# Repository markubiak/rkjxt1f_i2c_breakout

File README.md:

Alps RKJXT1F42001 7-Way Switch and Encoder I2C Breakout
-------------------------------------------------------

I2C breakout for Alps RKJXT1F42001 using Adafruit Seesaw library on the SAMD09.
Schematic is a copy of the I2C "Stemma QT" Rotary Encoder breakout board
(product 4991), though the NeoPixel and 2x STEMMA QT (JST SH 4-pin) connectors
had to be dropped due to layout constraints. The RKJXT1F is a significantly
larger through-hole device than the rotary encoder and the Stemma QT connectors
simply would not fit in their original locations. However, identical board
shape (1in x 1in) and mounting holes were retained. Due to an oversight, the
pin ordering in the through-hole connection was flipped from the reference
design.

Pins were kept the same as the reference design, so the firmware built on main
branch of adafruit/seesaw works laregly correctly. There is a difference in how
the RKJXT1F handles the rotary encoding compared to typical encoders, so a fork
of the seesaw library is pushed and pending merge back to main. With the
updated firmware, the I2C protocol works as intended. The GPIO Seesaw registers
can be used for the new A/B/C/D pins.

| Direction | GPIO Number |
|-----------|-------------|
| A         | 16          |
| B         | 17          |
| C         | 7           |
| D         | 2           |
| PUSH      | 24          |

The logic to handle the directions is simple enough to not require integration
into the seesaw library. Per the RKJXT1F datasheet, when PUSH goes active
(low), check if any of A/B/C/D are also active (low). If so, it's a directional
press. Else, it was a PUSH.

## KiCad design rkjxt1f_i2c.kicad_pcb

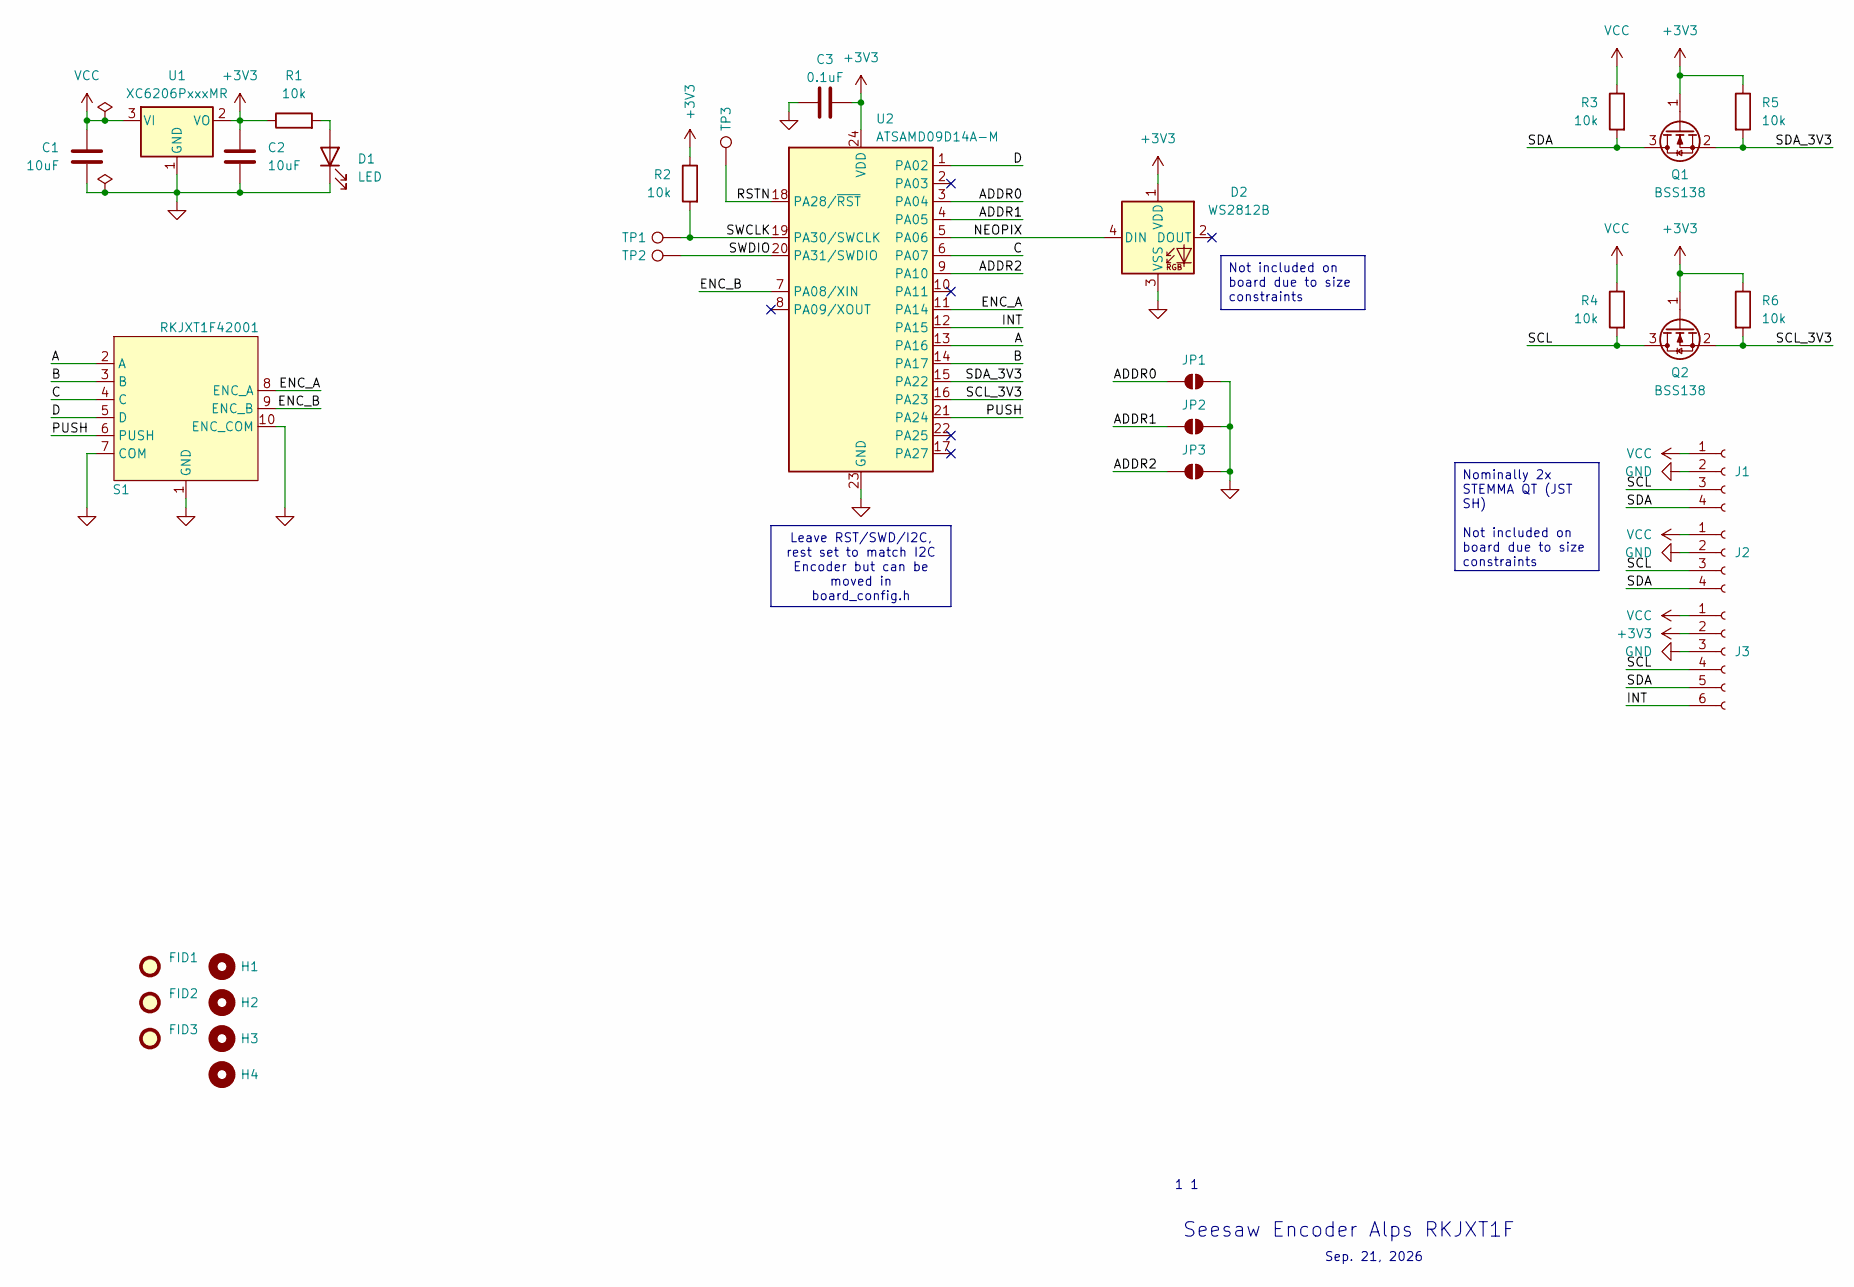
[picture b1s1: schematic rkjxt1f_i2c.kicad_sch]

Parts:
C1, C2: 10uF; C_0805_2012Metric
C3: 0.1uF; C_0603_1608Metric
D1: LED; LED_0805_2012Metric
D2: WS2812B; LED_WS2812B_PLCC4_5.0x5.0mm_P3.2mm
FID1, FID2, FID3: Fiducial; Fiducial_0.5mm_Mask1mm
H1, H2, H3, H4: MountingHole_Pad; MountingHole_2.5mm
J1, J2: Conn_01x04_Socket; JST_SH_BM04B-SRSS-TB_1x04-1MP_P1.00mm_Vertical
J3: Conn_01x06_Socket; PinHeader_1x06_P2.54mm_Vertical
JP1: A0; SolderJumper-2_P1.3mm_Open_TrianglePad1.0x1.5mm
JP2: A1; SolderJumper-2_P1.3mm_Open_TrianglePad1.0x1.5mm
JP3: A2; SolderJumper-2_P1.3mm_Open_TrianglePad1.0x1.5mm
Q1, Q2: BSS138; SOT-23
R1, R2, R3, R4, R5, R6: 10k; R_0603_1608Metric
S1: RKJXT1F42001
TP1, TP2, TP3: TestPoint; TestPoint_Pad_D1.5mm
U1: XC6206PxxxMR; SOT-23-3
U2: ATSAMD09D14A-M; QFN-24-1EP_4x4mm_P0.5mm_EP2.6x2.6mm

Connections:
+3V3: C2.1, C3.2, D2.1 (VDD), J3.2, Q1.1 (G), Q2.1 (G), R1.1, R2.1, R5.1, R6.1, U1.2 (VO), U2.24 (VDD)
/A: S1.2 (A), U2.13 (PA16)
/ADDR0: JP1.1 (A), U2.3 (PA04)
/ADDR1: JP2.1 (A), U2.4 (PA05)
/ADDR2: JP3.1 (A), U2.9 (PA10)
/B: S1.3 (B), U2.14 (PA17)
/C: S1.4 (C), U2.6 (PA07)
/D: S1.5 (D), U2.1 (PA02)
/ENC_A: S1.8 (ENC_A), U2.11 (PA14)
/ENC_B: S1.9 (ENC_B), U2.7 (PA08/XIN)
/INT: J3.6, U2.12 (PA15)
/NEOPIX: D2.4 (DIN), U2.5 (PA06)
/PUSH: S1.6 (PUSH), U2.21 (PA24)
/RSTN: TP3.1, U2.18 (PA28/~RST)
/SCL: J1.3, J2.3, J3.4, Q2.3 (D), R4.2
/SCL_3V3: Q2.2 (S), R6.2, U2.16 (PA23)
/SDA: J1.4, J2.4, J3.5, Q1.3 (D), R3.2
/SDA_3V3: Q1.2 (S), R5.2, U2.15 (PA22)
/SWCLK: R2.2, TP1.1, U2.19 (PA30/SWCLK)
/SWDIO: TP2.1, U2.20 (PA31/SWDIO)
GND: C1.2, C2.2, C3.1, D1.1 (K), D2.3 (VSS), J1.2, J2.2, J3.3, JP1.2 (B), JP2.2 (B), JP3.2 (B), S1.1 (GND), S1.7 (COM), S1.10 (ENC_COM), U1.1 (GND), U2.23 (GND), U2.25
unnamed: D1.2 (A), R1.2
VCC: C1.1, J1.1, J2.1, J3.1, R3.1, R4.1, U1.3 (VI)

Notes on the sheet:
1 1
Sep. 21, 2026
Seesaw Encoder Alps RKJXT1F
Leave RST/SWD/I2C, rest set to match I2C Encoder but can be moved in board_config.h
Not included on board due to size constraints
Nominally 2x STEMMA QT (JST SH) Not included on board due to size constraints

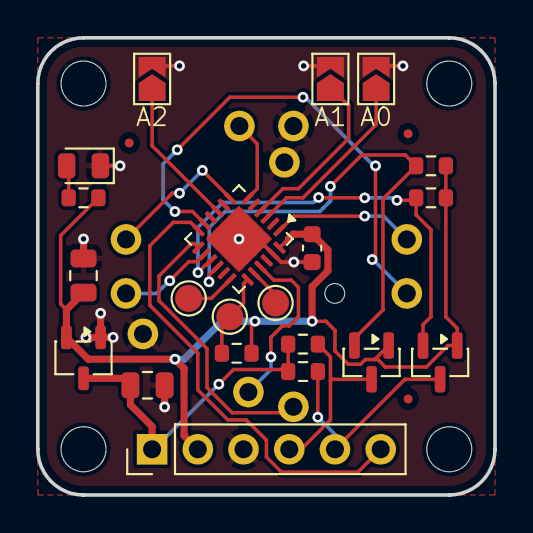
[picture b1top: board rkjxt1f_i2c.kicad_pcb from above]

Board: 2 copper layers, 25.4 x 25.4 mm, 29 parts (1 on the bottom side), 22 nets.
